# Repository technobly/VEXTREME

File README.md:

VEXTREME Vectrex Multicart
===

We're carrying on and pushing forward the amazing work of [Sprite_tm](http://spritesmods.com/?art=veccart&page=1) and his Extreme Vectrex Multicart. He posted the code (GPLv3 License) and lots of screens of the PCB/initial schematic, but he never released the PCB. It's a great base for an inexpensive and open vectrex multicart, for developers and players alike!

> **This fork adds VXE** - loadable co-op game payloads, so a game is one `.vxe` file on the card instead of a firmware rebuild. It is a build option (`VXE=0` builds the regular firmware as upstream). See [docs/vxe/](docs/vxe/README.md).

:warning: Please read this NOTICE of Current Development :warning:
===

**This project is a work in progress, and is not ready for mass production.**  Please observe the currently [posted issues](https://github.com/technobly/vextreme/issues) and there may be more lurking that are not yet identified.  The hardware and software is evolving.  You are free to build any version, contribute and/or follow along.  Please note that support of these pre-releases will be very limited and if you embark on an epic adventure to build one or a few, you should feel comfortable with this type of embedded hardware and software development.  There will be road bumps, but the journey is half the fun of the destination.  When things appear to be stable and we've worked out most of the kinks, we'll change the version to v1.0.  Only then is it advisable to mass produce, after building and testing a prototype first... so you know what you are getting yourself into.

3D Renders
===

Video Updates
===

Be sure to subscribe to my Youtube channel for updates!  Here's my [Vectrex playlist](https://www.youtube.com/watch?v=zkJ-z77fJCw&list=PL7MgXfpGKg6CCaIQejZVb5CsTg3-5mHU0&index=1) if you want to stay laser focused on this project.

VEXTREME Discord Server
===
Join the [VEXTREME Discord server](https://discord.gg/VDssGVJ) to chat with us about the development

BOM and Parts ordering
===

All the parts are described in Bill of Materials [vextreme-v0.x.csv](bom/)

Also, you can use this [Digi-Key shared cart](https://www.digikey.com/short/zpdmtp) if you're in a hurry.  It has will have part references right on the packages for you!

Ordering PCB's
===

OSHPark is a good place to order with purple or the new "after dark" theme color scheme.  You can upload the KiCad [vextreme.kicad_pcb](hardware/vextreme.kicad_pcb) there directly.  I would download this entire Github repo ZIP file first though instead of just trying to save the PCB file from your browser.

Another way to order PCB's is by using the included [gerbers-vextreme-v0.x.zip](gerbers) and uploading those with all of the necessary specs to companies like [PCBWay](https://www.pcbway.com) or [JLCPCB](https://jlcpcb.com)

Building and Flashing STM firmware
===

### This assumes you have these prerequisits installed:

- Docker
- dfu-util
- Make
- Windows will also require these [Zadig instructions](https://github.com/profezzorn/ProffieOS/wiki/zadig)

### Build the stm32-build docker image
```
code/stm32 $ make docker-build
```

### Connect the 2-pin jumper JP1 and then connect the cart to USB

### Check if your computer sees the STM32
```
$ dfu-util -l

dfu-util 0.9

Copyright 2005-2009 Weston Schmidt, Harald Welte and OpenMoko Inc.
Copyright 2010-2019 Tormod Volden and Stefan Schmidt
This program is Free Software and has ABSOLUTELY NO WARRANTY
Please report bugs to http://sourceforge.net/p/dfu-util/tickets/

Deducing device DFU version from functional descriptor length
Found DFU: [0483:df11] ver=2200, devnum=22, cfg=1, intf=0, path="20-1.4.3", alt=3, name="@Device Feature/0xFFFF0000/01*004 e", serial="123412341234"
Found DFU: [0483:df11] ver=2200, devnum=22, cfg=1, intf=0, path="20-1.4.3", alt=2, name="@OTP Memory /0x1FFF7800/01*512 e,01*016 e", serial="123412341234"
Found DFU: [0483:df11] ver=2200, devnum=22, cfg=1, intf=0, path="20-1.4.3", alt=1, name="@Option Bytes  /0x1FFFC000/01*016 e", serial="123412341234"
Found DFU: [0483:df11] ver=2200, devnum=22, cfg=1, intf=0, path="20-1.4.3", alt=0, name="@Internal Flash  /0x08000000/04*016Kg,01*064Kg,03*128Kg", serial="123412341234"
```

### Flash the UF2 Bootloader via dfu-util
```
uf2-stm32f $ dfu-util -a 0 -d 0483:df11 -s 0x08000000:leave -D bootloader.bin
```

### Build and flash the STM32 UF2 image via dfu-util
```
code/stm32 $ make clean all uf2 flash-uf2 USE_HW=v1.0 USE_UF2=1

// NOTE: Use either v0.2, v0.3, v0.4 or v1.0 above depending on which hardware version you have.
// NOTE: You may use v0.3 if you make the proper mods to your v0.2 board.  See "Modifying v0.2 to v0.3"

// You should end up with something like this

Downloading to address = 0x08004000, size = 134144
Download    [=========================] 100%        134144 bytes
Download done.
File downloaded successfully
```

### Remove the cart from USB and remove the jumper (install it on one pin so you don't lose it)

Adding Vectrex Game ROMs (Binaries)
===

- Create a directory on your multicart called `roms/`

- Add your first binaries there, may I suggest: [Beluga Dreams](https://8-bit-waves.itch.io/beluga-dreams) and [Vec-Man](http://eiti.fh-pforzheim.de/personen/johannsen/projektlabor/vectrex_2019/vectrex_game_vec_man.htm) ?

Hall of Fame
===

If you build one of these, be sure to send me a message with your build pics showing your working VEXTREME multicart!  Or better yet, check out the [hall of fame format here](hall-of-fame/) and submit a PR (please and thank you!)

Credits
===

Everyone who has contributed to this project, with a short summary of their contributions can be found here [CREDITS](CREDITS.md)

LICENSE
===

GPLv3 - essentially you must keep this open, all changes must be disclosed and shared.  Full [LICENSE here](LICENSE) and [TL;DR summary here](https://tldrlegal.com/license/gnu-general-public-license-v3-(gpl-3))

Docs
===

A collection of how-tos and lessons learned lives in [docs/](docs/):

- [Firmware Updates](docs/firmware-updates.md) - update VEXTREME firmware over USB with a `VEXTREME.uf2` file
- [Developer Mode](docs/developer-mode.md) - flash a single game over USB and run it immediately
- [Lazy Developer](docs/lazy-developer.md) - automatically ejects the USB drive when the Vectrex is turned on
- [Cart Options](docs/cart-options.md) - per-game `.ini` files to enable cartridge RAM
- [Datasheets](docs/datasheets/) - STM32F411 datasheet and reference manual
- [VXE](docs/vxe/README.md) - loadable co-op game payloads: how they work, the two flash layouts, how to build a game

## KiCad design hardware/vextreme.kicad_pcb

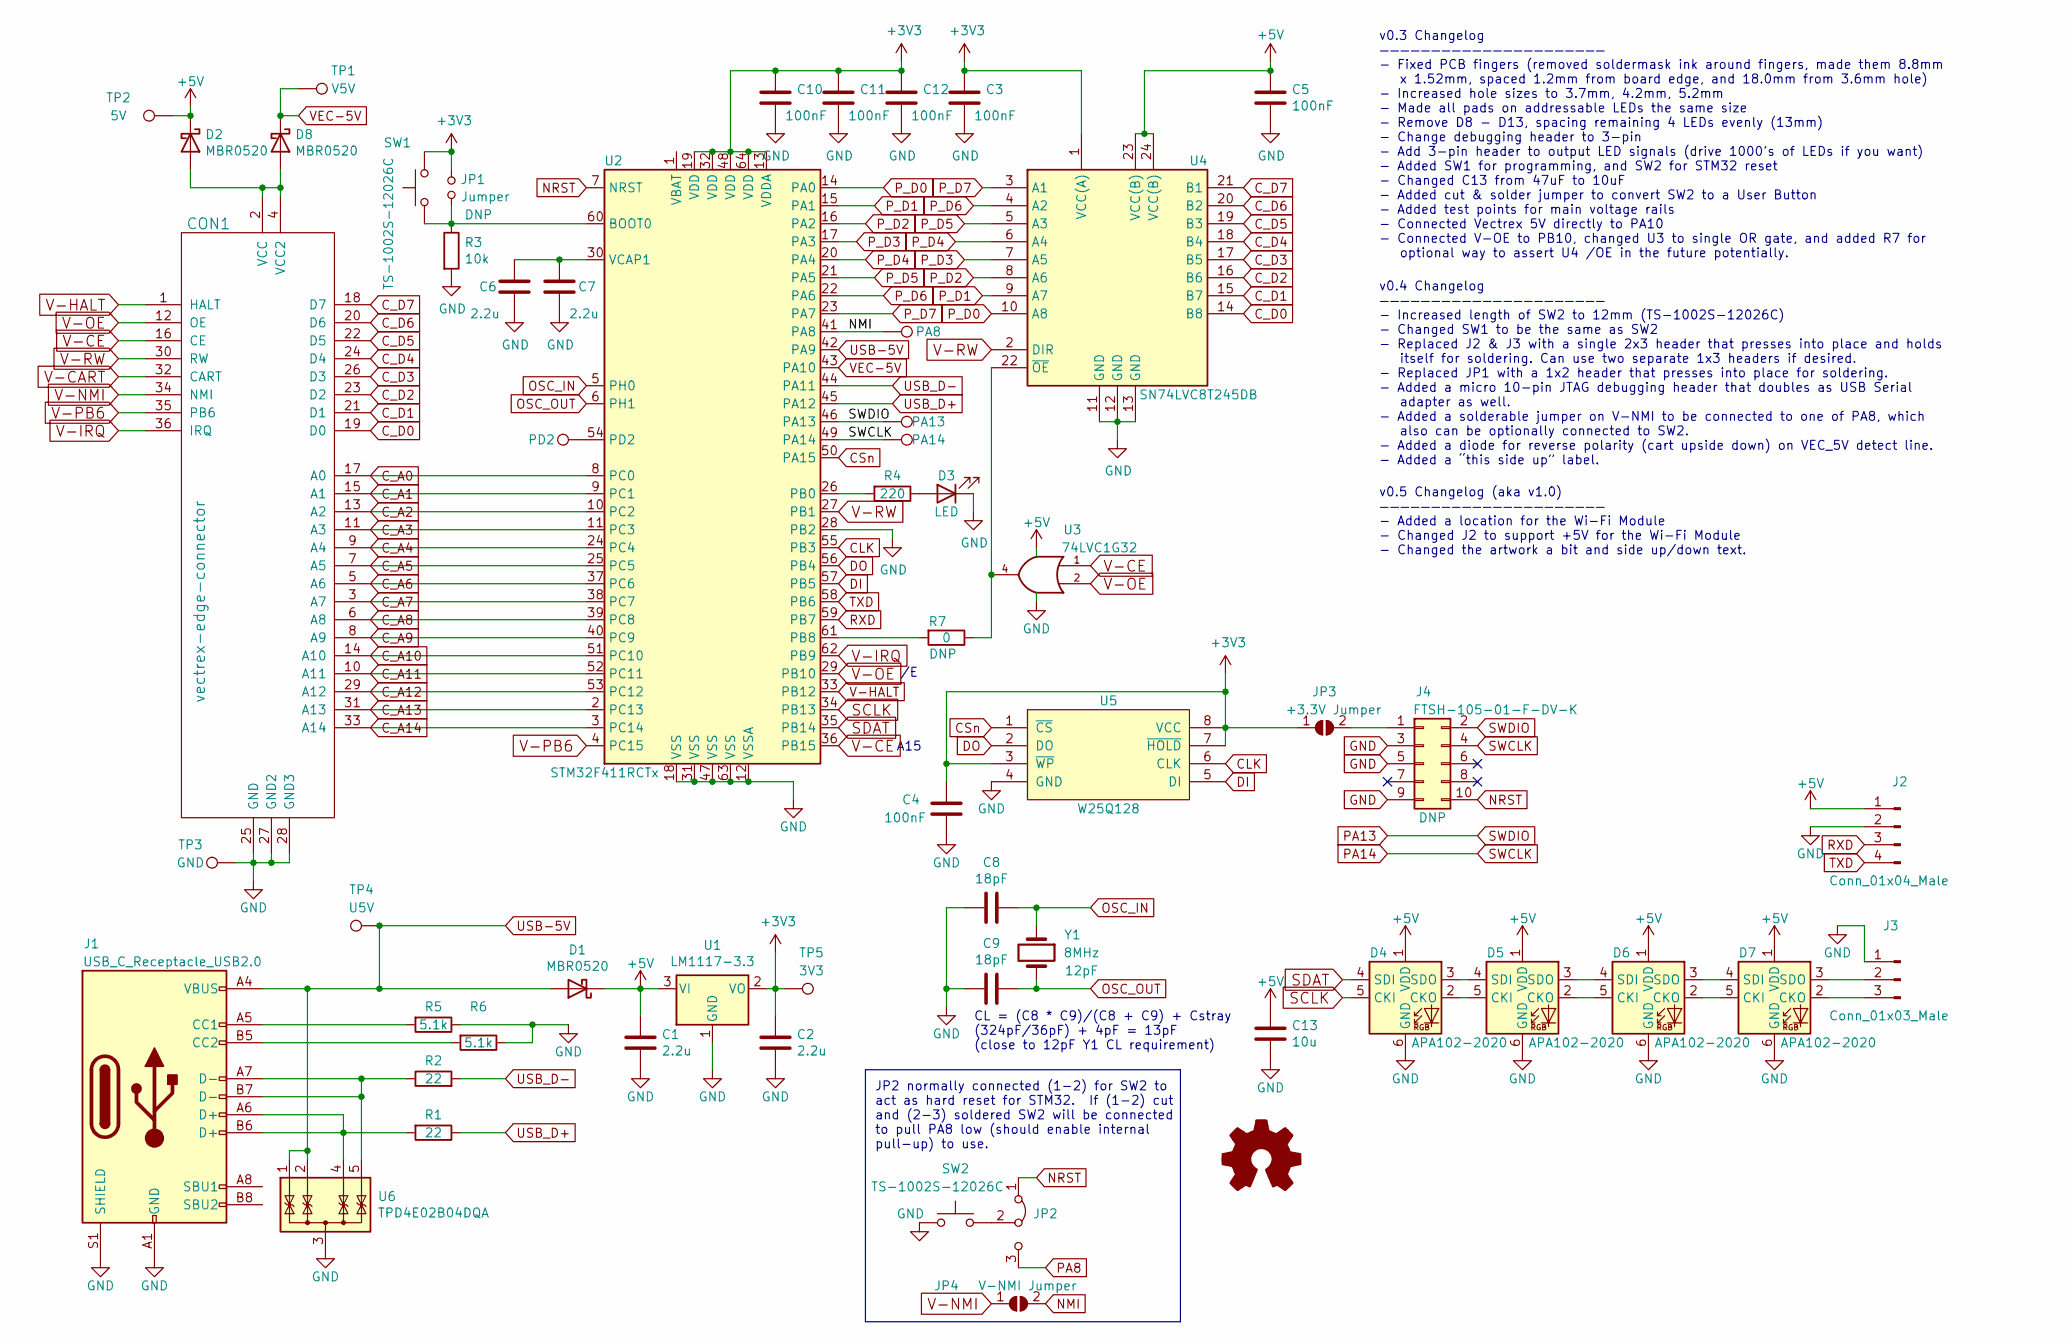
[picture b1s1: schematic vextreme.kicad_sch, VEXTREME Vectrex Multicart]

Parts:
C1, C2, C6, C7: 2.2u; C_0805_2012Metric_Pad1.15x1.40mm_HandSolder
C3, C4, C5, C10, C11, C12: 100nF; C_0805_2012Metric_Pad1.15x1.40mm_HandSolder
C8, C9: 18pF; C_0805_2012Metric_Pad1.15x1.40mm_HandSolder
C13: 10u; C_0805_2012Metric_Pad1.15x1.40mm_HandSolder
CON1: vectrex-edge-connector; vectrex-edge-connector-thinner-no-soldermask
D1, D2, D8: MBR0520; D_SOD-123
D3: LED; LED_0805_2012Metric_Pad1.15x1.40mm_HandSolder
D4, D5, D6, D7: APA102-2020; LED-APA102-2020_6_REV_2
J1: USB_C_Receptacle_USB2.0; USB_C_Receptacle_HRO_TYPE-C-31-M-12
J2: Conn_01x04_Male; PinHeader_1x04_P2.54mm_Vertical_Odd_Even
J3: Conn_01x03_Male; PinHeader_1x03_P2.54mm_Vertical_Odd_Even
J4: FTSH-105-01-F-DV-K; CONN5X2_1.27
JP1: Jumper; PinHeader_1x02_P2.54mm_Vertical_Odd_Even
JP2: Jumper_3_Bridged12; SolderJumper-3_P1.3mm_Bridged12_RoundedPad1.0x1.5mm_NumberL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
JP3: +3.3V Jumper; SolderJumper-2_P1.3mm_Open_RoundedPad1.0x1.5mm
JP4: V-NMI Jumper; SolderJumper-2_P1.3mm_Open_RoundedPad1.0x1.5mm
R1, R2: 22; R_0805_2012Metric_Pad1.15x1.40mm_HandSolder
R3: 10k; R_0805_2012Metric_Pad1.15x1.40mm_HandSolder
R4: 220; R_0805_2012Metric_Pad1.15x1.40mm_HandSolder
R5, R6: 5.1k; R_0805_2012Metric_Pad1.15x1.40mm_HandSolder
R7: 0; R_0805_2012Metric_Pad1.15x1.40mm_HandSolder
SP1: PA8; SparePin_1x01_P2.54mm_Vertical
SP2: PA13; SparePin_1x01_P2.54mm_Vertical
SP3: PA14; SparePin_1x01_P2.54mm_Vertical
SP4: PD2; SparePin_1x01_P2.54mm_Vertical
SW1, SW2: TS-1002S-12026C; SW_Push_1P1T_NO_6x6mm_H12.0mm
TP1: V5V; TestPoint_Pad_D1.5mm
TP2: 5V; TestPoint_Pad_D1.5mm
TP3: GND; TestPoint_Pad_D1.5mm
TP4: U5V; TestPoint_Pad_D1.5mm
TP5: 3V3; TestPoint_Pad_D1.5mm
U1: LM1117-3.3; SOT-223-3_TabPin2
U2: STM32F411RCTx; LQFP-64_10x10mm_P0.5mm
U3: 74LVC1G32; SOT-23-5_HandSoldering
U4: SN74LVC8T245DB; SSOP-24_5.3x8.2mm_P0.65mm
U5: W25Q128; SOIC-8_5.23x5.23mm_P1.27mm
U6: TPD4E02B04DQA; USON-10_2.5x1.0mm_P0.5mm_passthrough
Y1: 8MHz; Crystal_SMD_5032-2Pin_5.0x3.2mm_HandSoldering

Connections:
+3V3: C2.1, C3.1, C4.1, C10.1, C11.1, C12.1, JP1.2, JP3.1 (A), SW1.2, TP5.1, U1.2 (VO), U2.13 (VDDA), U2.19 (VDD), U2.32 (VDD), U2.48 (VDD), U2.64 (VDD), U4.1 (VCC(A)), U5.3 (~WP), U5.7 (~HOLD), U5.8 (VCC)
+5V: C1.1, C5.1, C13.1, D1.1 (K), D2.1 (K), D4.1 (VDD), D5.1 (VDD), D6.1 (VDD), D7.1 (VDD), J2.1, TP2.1, U1.3 (VI), U3.5 (VCC), U4.23 (VCC(B)), U4.24 (VCC(B))
CLK: U2.55 (PB3), U5.6 (CLK)
CSn: U2.50 (PA15), U5.1 (~CS)
C_A0: CON1.17 (A0), U2.8 (PC0)
C_A1: CON1.15 (A1), U2.9 (PC1)
C_A2: CON1.13 (A2), U2.10 (PC2)
C_A3: CON1.11 (A3), U2.11 (PC3)
C_A4: CON1.9 (A4), U2.24 (PC4)
C_A5: CON1.7 (A5), U2.25 (PC5)
C_A6: CON1.5 (A6), U2.37 (PC6)
C_A7: CON1.3 (A7), U2.38 (PC7)
C_A8: CON1.6 (A8), U2.39 (PC8)
C_A9: CON1.8 (A9), U2.40 (PC9)
C_A10: CON1.14 (A10), U2.51 (PC10)
C_A11: CON1.10 (A11), U2.52 (PC11)
C_A12: CON1.29 (A12), U2.53 (PC12)
C_A13: CON1.31 (A13), U2.2 (PC13)
C_A14: CON1.33 (A14), U2.3 (PC14)
C_D0: CON1.19 (D0), U4.14 (B8)
C_D1: CON1.21 (D1), U4.15 (B7)
C_D2: CON1.23 (D2), U4.16 (B6)
C_D3: CON1.26 (D3), U4.17 (B5)
C_D4: CON1.24 (D4), U4.18 (B4)
C_D5: CON1.22 (D5), U4.19 (B3)
C_D6: CON1.20 (D6), U4.20 (B2)
C_D7: CON1.18 (D7), U4.21 (B1)
DI: U2.57 (PB5), U5.5 (DI)
DO: U2.56 (PB4), U5.2 (DO)
GND: C1.2, C2.2, C3.2, C4.2, C5.2, C6.2, C7.2, C8.2, C9.2, C10.2, C11.2, C12.2, C13.2, CON1.25 (GND), CON1.27 (GND2), CON1.28 (GND3), D3.1 (K), D4.6 (GND), D5.6 (GND), D6.6 (GND), D7.6 (GND), J1.A1 (GND), J1.A12 (GND), J1.B1 (GND), J1.B12 (GND), J1.S1 (SHIELD), J2.2, J3.1, J4.3, J4.5, J4.9, R3.2, R5.1, R6.1, SW2.1, TP3.1, U1.1 (GND), U2.12 (VSSA), U2.18 (VSS), U2.28 (PB2), U2.31 (VSS), U2.47 (VSS), U2.63 (VSS), U3.3 (GND), U4.11 (GND), U4.12 (GND), U4.13 (GND), U5.4 (GND), U6.3 (G)
NMI: JP4.2 (B), SP1.1, U2.41 (PA8)
NRST: J4.10, JP2.1 (A), U2.7 (NRST)
unnamed: C6.1, C7.1, U2.30 (VCAP1)
unnamed: CON1.2 (VCC), CON1.4 (VCC2), D2.2 (A), D8.2 (A)
unnamed: D3.2 (A), R4.1
unnamed: D4.2 (CKO), D5.5 (CKI)
unnamed: D4.3 (SDO), D5.4 (SDI)
unnamed: D5.2 (CKO), D6.5 (CKI)
unnamed: D5.3 (SDO), D6.4 (SDI)
unnamed: D6.2 (CKO), D7.5 (CKI)
unnamed: D6.3 (SDO), D7.4 (SDI)
unnamed: D7.2 (CKO), J3.3
unnamed: D7.3 (SDO), J3.2
unnamed: J1.A5 (CC1), R5.2
unnamed: J1.A6 (D+), J1.B6 (D+), R1.2, U6.4 (IO3)
unnamed: J1.A7 (D-), J1.B7 (D-), R2.1, U6.5 (IO4)
unnamed: J1.B5 (CC2), R6.2
unnamed: J4.1, JP3.2 (B)
unnamed: JP1.1, R3.1, SW1.1, U2.60 (BOOT0)
unnamed: JP2.2 (C), SW2.2
unnamed: R4.2, U2.26 (PB0)
unnamed: R7.1, U3.4, U4.22 (~OE)
unnamed: R7.2, U2.61 (PB8)
unnamed: SP4.1, U2.54 (PD2)
OSC_IN: C8.1, U2.5 (PH0), Y1.1
OSC_OUT: C9.1, U2.6 (PH1), Y1.2
PA8: JP2.3 (B)
PA13: J4.2, SP2.1, U2.46 (PA13)
PA14: J4.4, SP3.1, U2.49 (PA14)
P_D0: U2.14 (PA0), U4.10 (A8)
P_D1: U2.15 (PA1), U4.9 (A7)
P_D2: U2.16 (PA2), U4.8 (A6)
P_D3: U2.17 (PA3), U4.7 (A5)
P_D4: U2.20 (PA4), U4.6 (A4)
P_D5: U2.21 (PA5), U4.5 (A3)
P_D6: U2.22 (PA6), U4.4 (A2)
P_D7: U2.23 (PA7), U4.3 (A1)
RXD: J2.3, U2.59 (PB7)
SCLK: D4.5 (CKI), U2.34 (PB13)
SDAT: D4.4 (SDI), U2.35 (PB14)
TXD: J2.4, U2.58 (PB6)
USB-5V: D1.2 (A), J1.A4 (VBUS), J1.A9 (VBUS), J1.B4 (VBUS), J1.B9 (VBUS), TP4.1, U2.42 (PA9), U6.1 (IO1), U6.2 (IO2)
USB_D+: R1.1, U2.45 (PA12)
USB_D-: R2.2, U2.44 (PA11)
V-CART: CON1.32 (CART)
V-CE: CON1.16 (CE), U2.36 (PB15), U3.1
V-HALT: CON1.1 (HALT), U2.33 (PB12)
V-IRQ: CON1.36 (IRQ), U2.62 (PB9)
V-NMI: CON1.34 (NMI), JP4.1 (A)
V-OE: CON1.12 (OE), U2.29 (PB10), U3.2
V-PB6: CON1.35 (PB6), U2.4 (PC15)
V-RW: CON1.30 (RW), U2.27 (PB1), U4.2 (DIR)
VEC-5V: D8.1 (K), TP1.1, U2.43 (PA10)

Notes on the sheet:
v0.5 Changelog (aka v1.0) —————————————————————— - Added a location for the Wi-Fi Module - Changed J2 to support +5V for the Wi-Fi Module - Changed the artwork a bit and side up/down text.
CL = (C8 * C9)/(C8 + C9) + Cstray (324pF/36pF) + 4pF = 13pF (close to 12pF Y1 CL requirement)
v0.3 Changelog —————————————————————— - Fixed PCB fingers (removed soldermask ink around fingers, made them 8.8mm x 1.52mm, spaced 1.2mm from board edge, and 18.0mm from 3.6mm hole) - Increased hole sizes to 3.7mm, 4.2mm, 5.2mm - Made all pads on addressable LEDs the same size - Remove D8 - D13, sp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
v0.4 Changelog —————————————————————— - Increased length of SW2 to 12mm (TS-1002S-12026C) - Changed SW1 to be the same as SW2 - Replaced J2 & J3 with a single 2x3 header that presses into place and holds itself for soldering. Can use two separate 1x3 headers if desired. - Replaced JP1 with a 1x2 he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
JP2 normally connected (1-2) for SW2 to act as hard reset for STM32. If (1-2) cut and (2-3) soldered SW2 will be connected to pull PA8 low (should enable internal pull-up) to use.
A15

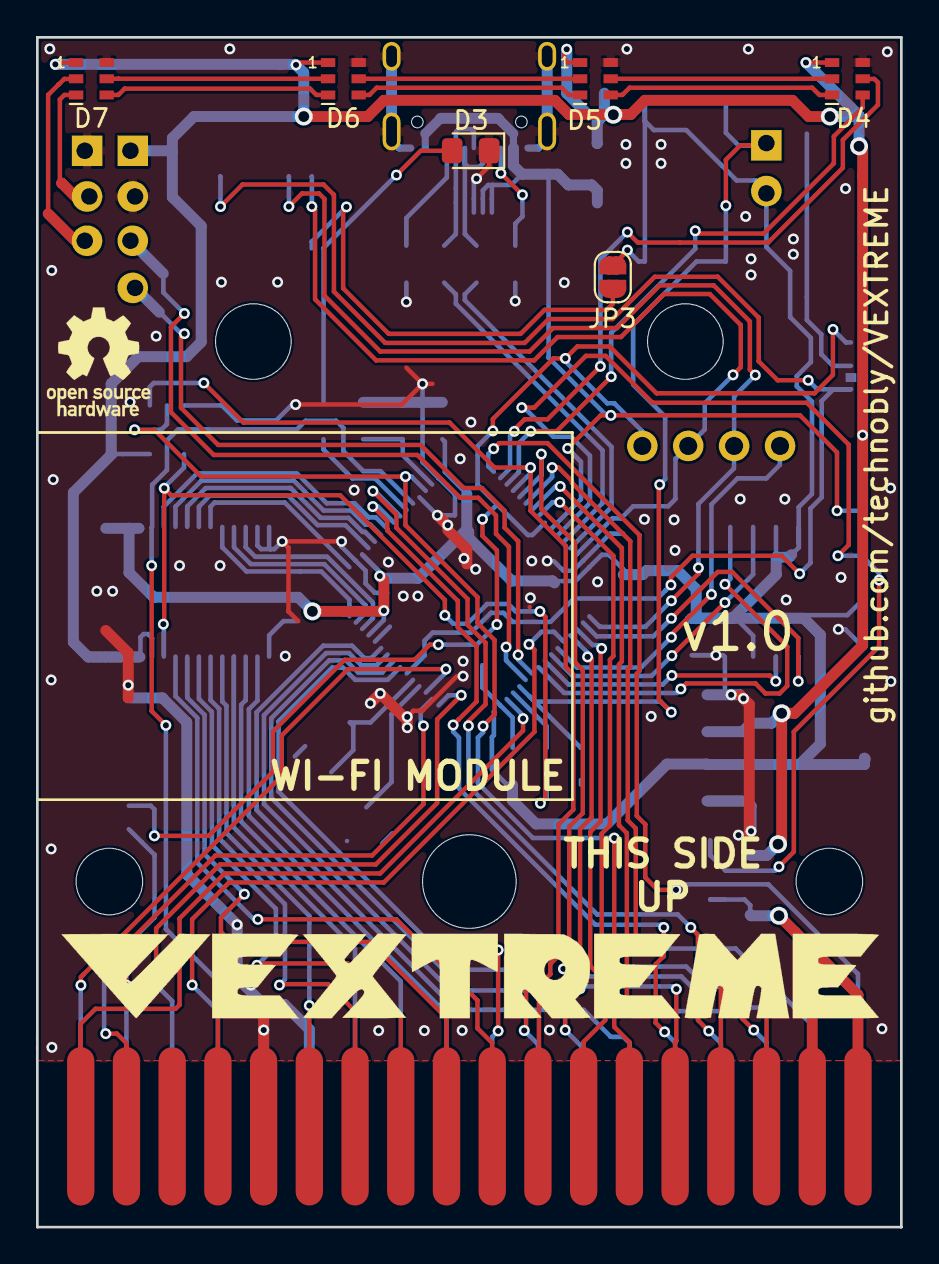
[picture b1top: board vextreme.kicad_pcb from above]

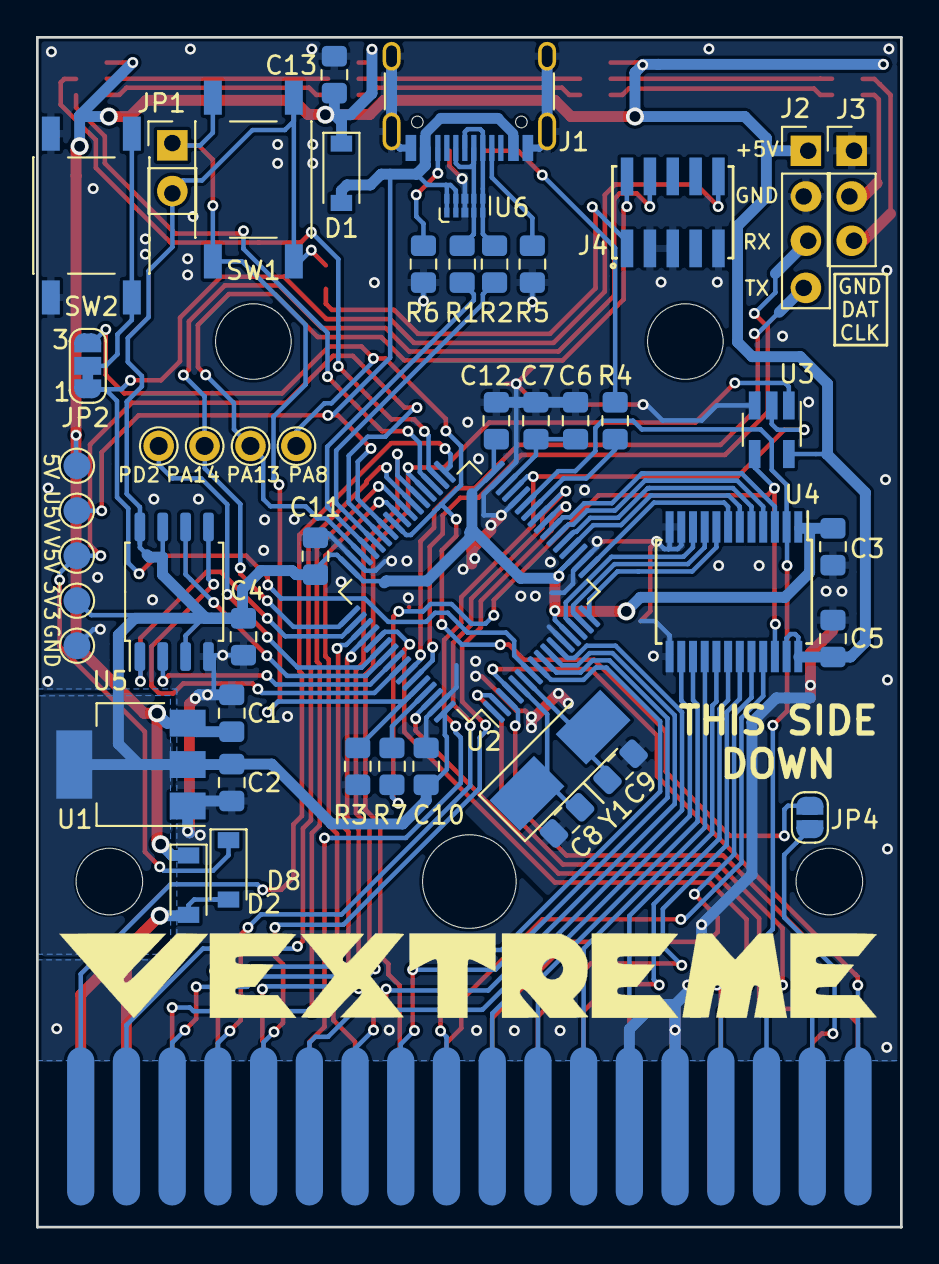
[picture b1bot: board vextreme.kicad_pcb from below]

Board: 2 copper layers, 48.0 x 66.1 mm, 60 parts (48 on the bottom side), 81 nets.

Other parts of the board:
hole1, hole3: Mounting_Hole_D3.7mm
hole2: Mounting_Hole_D5.2mm
hole4, hole5: Mounting_Hole_D4.2mm

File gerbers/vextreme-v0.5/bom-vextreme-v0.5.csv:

Item,Designator,Qty,Mfg part #,Manufacturer,Value,Footprint,Description,Type,Notes
1,"C1, C2, C6, C7",4,CL21F225ZAFNNNE,Samsung Electro-Mechanics,2.2u,"""0805""",Unpolarized capacitor,SMD,
2,"C3, C4, C5, C10, C11, C12",6,C0805C104K5RAC7800,Kemet,100nF,"""0805""",Unpolarized capacitor,SMD,
3,"C8, C9",2,CC0805JRNPO9BN180,YAGEO,18pF,"""0805""",Unpolarized capacitor,SMD,
4,C13,1,EMK212BJ106KG-T,Taiyo Yuden,10u,"""0805""",Unpolarized capacitor,SMD,
5,"D1, D2, D8",3,MBR0540,,MBR0540,SOD-123,"20V 0.5A Schottky Power Rectifier Diode, SOD-123",SMD,
6,D3,1,LTST-C170KRKT,Lite-On,LED,"""0805""",Red 631~639nm Light Emitting Diodes (LED),SMD,DNP
7,"D4, D5, D6, D7",4,,,APA102-2020,vextreme:LED-APA102-2020_6_REV_2,RGB LED with integrated controller,SMD,DNP
8,J1,1,TYPE-C-31-M-12,Korean Hroparts Elec,USB_C_Receptacle_USB2.0,vextreme:USB_C_Receptacle_HRO_TYPE-C-31-M-12,USB 2.0-only Type-C Receptacle connector,SMD,
9,J2,1,,,Conn_01x04_Male,vextreme:PinHeader_1x04_P2.54mm_Vertical_Odd_Even,"Generic connector, single row, 01x04, script generated (kicad-library-utils/schlib/autogen/connector/)",TH,DNP
10,J3,1,,,Conn_01x03_Male,vextreme:PinHeader_1x03_P2.54mm_Vertical_Odd_Even,"Generic connector, single row, 01x03, script generated (kicad-library-utils/schlib/autogen/connector/)",TH,DNP
11,J4,1,,,FTSH-105-01-F-DV-K,vextreme:CONN5X2_1.27,"Generic connector, double row, 02x05, odd/even pin numbering scheme (row 1 odd numbers, row 2 even numbers)",SMD,DNP
12,JP1,1,,,Jumper,vextreme:PinHeader_1x02_P2.54mm_Vertical_Odd_Even,"Jumper, normally open, small symbol",SMD,DNP
13,"R1, R2",2,RC0805FR-0722RL,YAGEO,22,"""0805""",Resistor,SMD,
14,R3,1,RC0805FR-0710KL,YAGEO,10k,"""0805""",Resistor,SMD,
15,R4,1,RC0805FR-07220RL,YAGEO,220,"""0805""",Resistor,SMD,
16,"R5, R6",2,RC0805FR-075K1L,YAGEO,5.1k,"""0805""",Resistor,SMD,
17,R7,1,,,0,"""0805""",Resistor,SMD,DNP
18,"SW1, SW2",2,TS-1002S-12026C,XUNPU,TS-1002S-12026C,vextreme:SW_Push_1P1T_NO_6x6mm_H12.0mm,"Push button switch, generic, two pins",SMD,
19,U1,1,LM1117MPX-3.3/NOPB,Texas Instruments,LM1117-3.3,Package_TO_SOT_SMD:SOT-223-3_TabPin2,"800mA Low-Dropout Linear Regulator, 3.3V fixed output, TO-220/TO-252/TO-263/SOT-223",SMD,
20,U2,1,STM32F411RCT6,STMicroelectronics,STM32F411RCTx,Package_QFP:LQFP-64_10x10mm_P0.5mm,"ARM Cortex-M4 MCU, 256KB flash, 128KB RAM, 100MHz, 1.7-3.6V, 50 GPIO, LQFP-64",SMD,
21,U3,1,SN74LVC1G32DBVR,Texas Instruments,74LVC1G32,vextreme:SOT-23-5_HandSoldering,"Single OR Gate, Low-Voltage CMOS",SMD,
22,U4,1,SN74LVC8T245DBR,Texas Instruments,SN74LVC8T245DB,Package_SO:SSOP-24_5.3x8.2mm_P0.65mm,"8-bit dual supply translating transceiver, 3-state, SSOP-24",SMD,
23,U5,1,W25Q128JVSIQ,Winbond Elec,W25Q128,Package_SO:SOIC-8_5.23x5.23mm_P1.27mm,External EEPROM with SPI interface in 8-pin package,SMD,
24,U6,1,TPD4E02B04DQAR,Texas Instruments,TPD4E02B04DQA,vextreme:USON-10_2.5x1.0mm_P0.5mm_passthrough,USB ESD,SMD,
25,Y1,1,7A08000006,TXC Corp,8MHz,Crystal:Crystal_SMD_5032-2Pin_5.0x3.2mm_HandSoldering,8MHz ±20ppm 12pF 80Ω SMD Crystal Resonators,SMD,

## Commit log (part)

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2020-05-02 Feature/55 High Score
2020-05-02 Adding highscore.c
2020-06-27 rename 'veccart' to 'stm32' for firmware and 'vextreme' for hardware, rename 'multicart' to 'menu'.
2020-12-12 normalize filemode to 100644 for all files
2020-12-12 updated Hall of Fame
2020-12-12 v0.24 Changelog
2021-03-03 Revamped menu with vector font, settings and screensaver
2021-03-05 Changes requested by maintainer
2021-03-06 Replace strcpy by strncpy
2021-03-06 Cleanup leftover
2021-03-13 remove rescue library and merge all schematic parts into a common vextreme.lib
2021-03-19 Fix LED brightness in solid color mode
2021-03-19 Fix LED color component calculation so it can reach 255
2021-03-19 Change MIT to GPL for new files
2021-03-21 Add settings.size,.ver and initialize routine, future-proof settings.bin by incr. to 1Ki
2021-03-21 whitespace changes
2021-03-21 Added a Credits Page
2021-03-22 whitespace and formatting
2021-04-30 Update to Credits Page
2021-04-30 add RAM support for Logo Lite, extends RAM range from 000 to 6ff
2021-06-19 New stm32 build container
    * Alpine-based
    * Uses latest official ARM toolchain (arm-none-eabi-gcc 10.2)
    * Add uf2conv.py and some make targets for supporting UF2 builds
2022-09-01 Added mp directory
    Created and files for Marcel Prisi directory, number 13 (ammended)
2023-08-21 remove herobrine
2025-08-10 fixes #38, 64kb bankswitched games work now
2025-08-26 reduce LED brightness by default, and let SETTINGS control
2025-08-26 updated Credits Page
2025-08-26 Enhance header parsing for high score and save via CRCVX as unique key, Fixes #74
2025-08-26 fixes crc for games of size evenly divisible by 4
2025-08-26 Added Cart Options INI files, as a start to enable RAM for specific games with specific address ranges
2025-08-26 adds convenient way to setup Wi-Fi with self-documenting wifi.txt file
2025-08-26 adds v1.0 to the build
2025-08-26 ignore .uf2 files
2025-08-26 adds v0.4 to the build
2025-08-26 Adds a new feature for v0.4 HW called Lazy Developer
2025-08-26 tony case changes
2025-08-26 system -> update firmware menu option for uf2
2025-08-26 uf2 changes
2025-09-05 update copyright to 2025
2025-09-05 some changes to support 10 LED vs. 4 LED VEXTREMEs, halt line easter egg
